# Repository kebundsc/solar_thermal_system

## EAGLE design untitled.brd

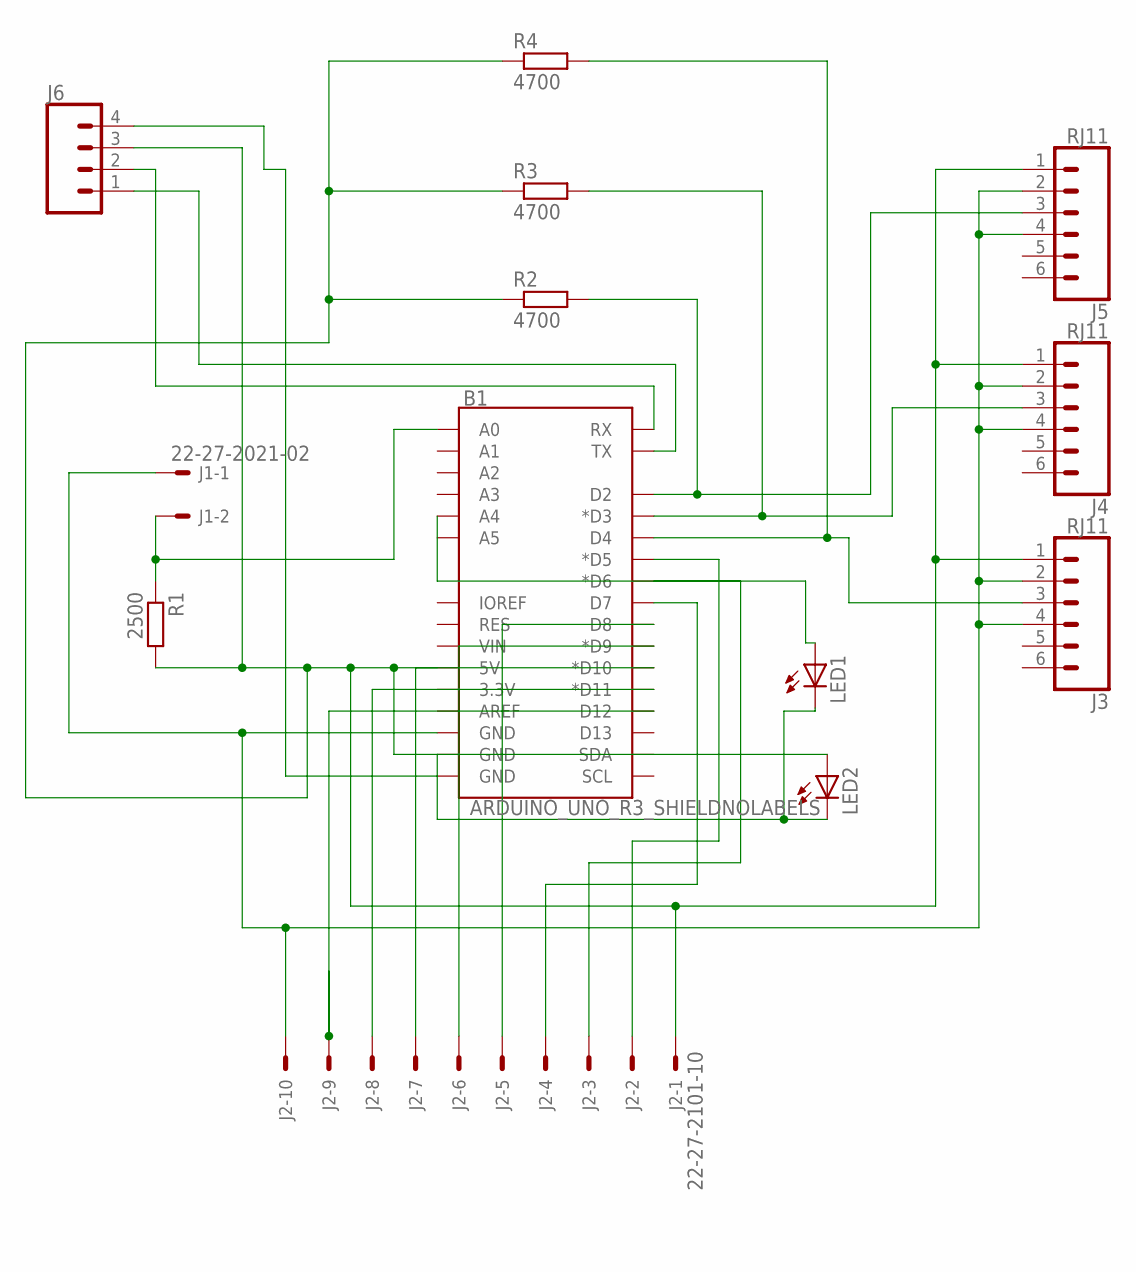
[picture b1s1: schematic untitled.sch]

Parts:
B1: ARDUINO_UNO_R3_SHIELDNOLABELS; UNO_R3_SHIELD_NOLABELS
J1: 22-27-2021-02; 6410-02
J2: 22-27-2101-10; 6410-10
J3, J4, J5: RJ11; RJ11-6
J6: CONN_04; 1X04
LED1, LED2: LED3MM
R1: 2500; R1206
R2, R3, R4: 4700; R1206

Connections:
unnamed: B1.5V, J2.1, J3.1, J4.1, J5.1, J6.3, LED2.A, R1.2, R2.1, R3.1, R4.1
unnamed: B1.GND@2 (GND), J1.1, J2.10, J3.2, J3.4, J4.2, J4.4, J5.2, J5.4
unnamed: B1.D12, J2.9
unnamed: B1.A0, J1.2, R1.1
unnamed: B1.D5 (*D5), J2.2
unnamed: B1.D6 (*D6), J2.3
unnamed: B1.D2, J5.3, R2.2
unnamed: B1.D3 (*D3), J4.3, R3.2
unnamed: B1.D4, J3.3, R4.2
unnamed: B1.D7, J2.4
unnamed: B1.D8, J2.5
unnamed: B1.D9 (*D9), J2.6
unnamed: B1.D10 (*D10), J2.7
unnamed: B1.D11 (*D11), J2.8
unnamed: B1.TX, J6.1
unnamed: B1.RX, J6.2
unnamed: B1.GND@0 (GND), J6.4
unnamed: B1.GND@1 (GND), LED1.K (C), LED2.K (C)
unnamed: B1.A4, LED1.A

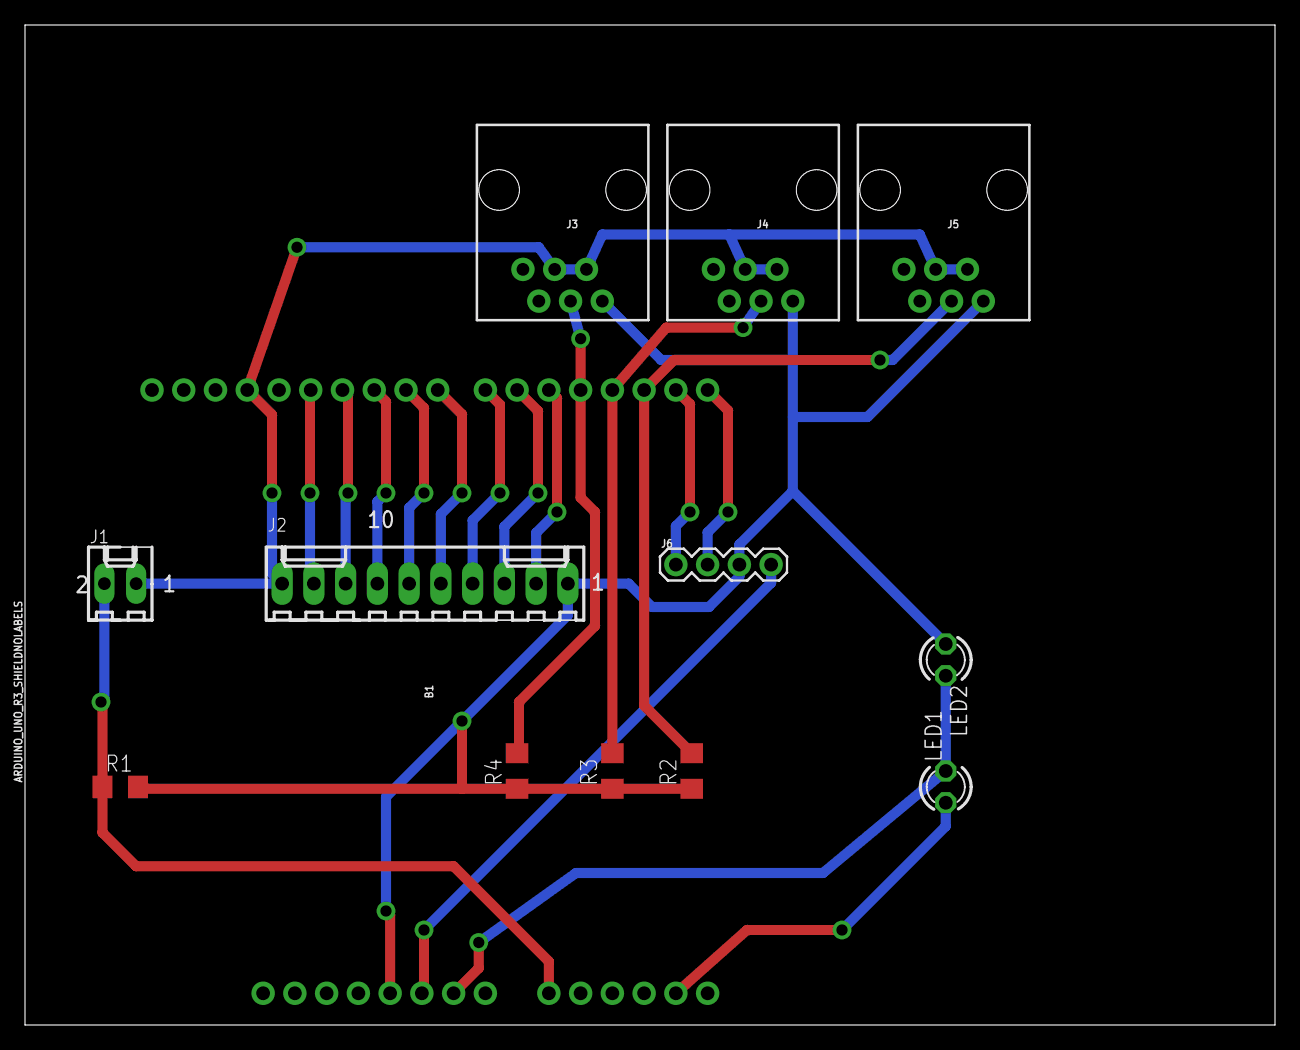
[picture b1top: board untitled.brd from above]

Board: 2 copper layers, 100.0 x 80.0 mm, 13 parts (0 on the bottom side), 19 nets.

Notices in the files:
parts and their libraries:
SparkFun-Boards: Licensing: Creative Commons ShareAlike 4.0 International - https://creativecommons.org/licenses/by-sa/4.0
